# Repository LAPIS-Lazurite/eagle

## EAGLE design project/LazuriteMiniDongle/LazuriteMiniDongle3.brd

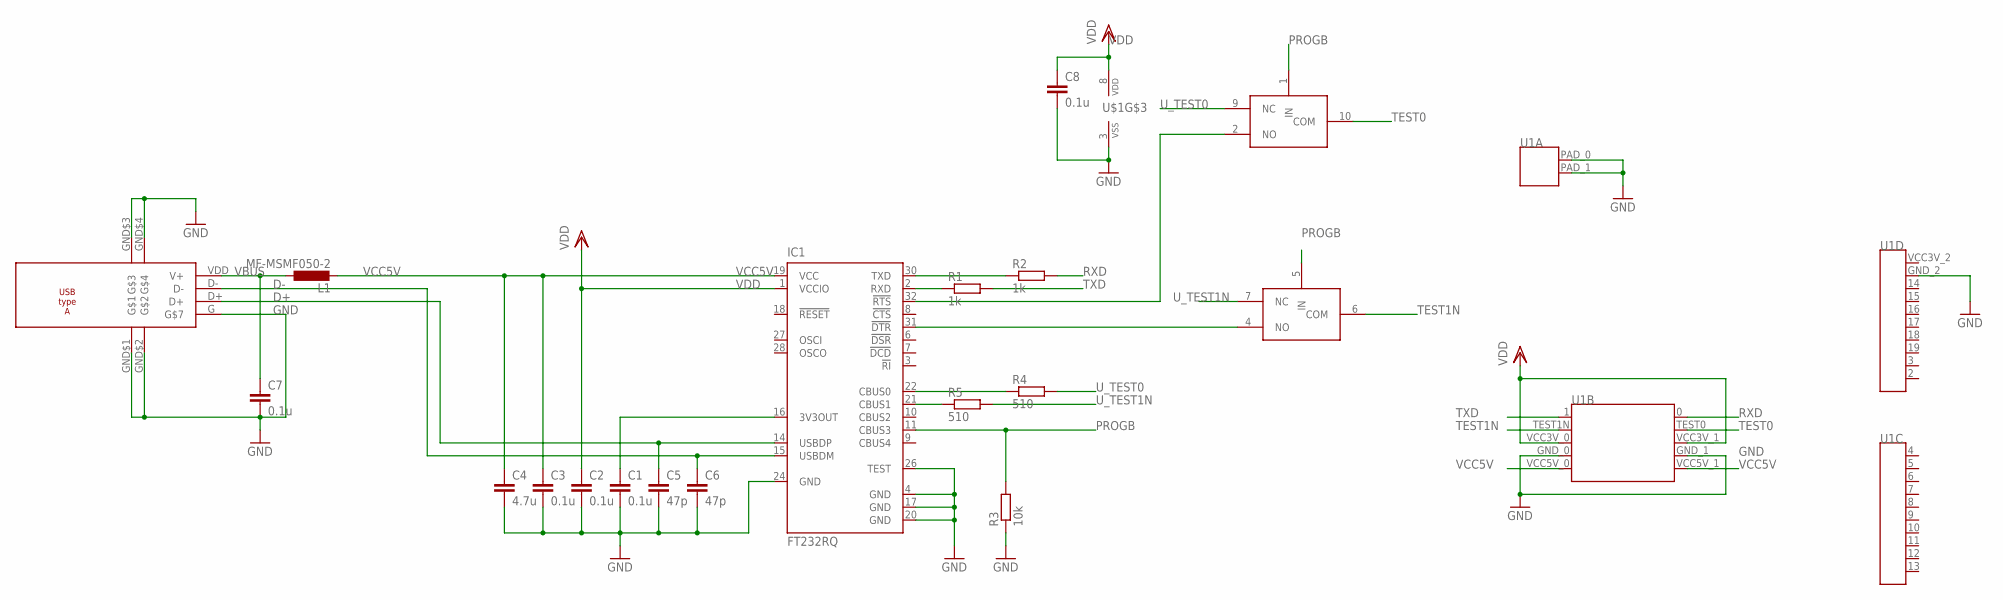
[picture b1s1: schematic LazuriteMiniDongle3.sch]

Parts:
C1, C2, C3, C7, C8: 0.1u; C0402
C4: 4.7u; C1608
C5, C6: 47p; C0402
IC1: FT232RQ; QFN32
L1: MF-MSMF050-2; L1812
R1, R2: 1k; R0402
R3: 10k; R0402
R4, R5: 510; R0402
U1: LAZURITE920JNOSILK; LAZURITE920J(NOSILK)
U$1: TI-TS5A23159; UQFN10
U$2: USB-TYPE-A; UP2-AH-TH

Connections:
D+: C5.1, IC1.14 (USBDP), U$2.D+
D-: C6.1, IC1.15 (USBDM), U$2.D-
GND: C1.2, C2.2, C3.2, C4.2, C5.2, C6.2, C7.2, C8.2, IC1.4 (GND), IC1.17 (GND), IC1.20 (GND), IC1.24 (GND), IC1.26 (TEST), R3.1, U1.GND_0, U1.GND_1, U1.GND_2, U1.PAD_0, U1.PAD_1, U$1.3 (VSS), U$2.G, U$2.GND$1, U$2.GND$2, U$2.GND$3, U$2.GND$4
unnamed: C1.1, IC1.16 (3V3OUT)
unnamed: IC1.32 (!RTS), U$1.2 (NO)
unnamed: IC1.2 (RXD), R1.1
unnamed: IC1.30 (TXD), R2.1
unnamed: IC1.21 (CBUS1), R5.1
unnamed: IC1.22 (CBUS0), R4.1
unnamed: IC1.31 (!DTR), U$1.4 (NO)
PROGB: IC1.11 (CBUS3), R3.2, U$1.1 (IN), U$1.5 (IN)
RXD: R2.2, U1.0
TEST0: U1.TEST0, U$1.10 (COM)
TEST1N: U1.TEST1N, U$1.6 (COM)
TXD: R1.2, U1.1
U_TEST0: R4.2, U$1.9 (NC)
U_TEST1N: R5.2, U$1.7 (NC)
VBUS: C7.1, L1.1, U$2.VDD (V+)
VCC5V: C3.1, C4.1, IC1.19 (VCC), L1.2, U1.VCC5V_0, U1.VCC5V_1
VDD: C2.1, C8.1, IC1.1 (VCCIO), U1.VCC3V_0, U1.VCC3V_1, U$1.8 (VDD)

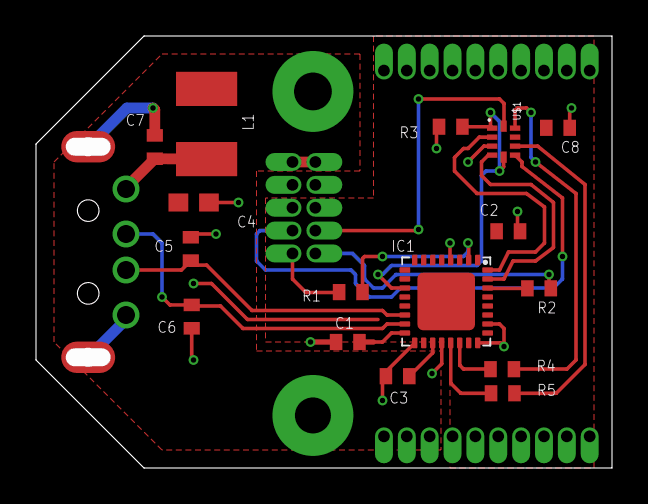
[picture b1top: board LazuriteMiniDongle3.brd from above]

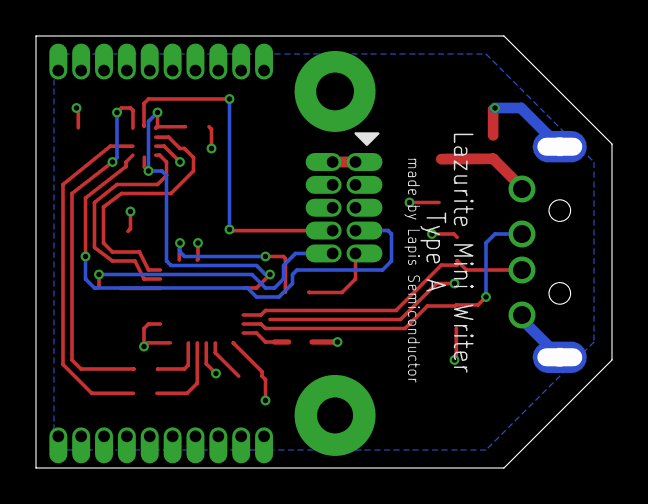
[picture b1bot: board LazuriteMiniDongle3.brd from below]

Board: 2 copper layers, 32.0 x 24.0 mm, 18 parts (2 on the bottom side), 20 nets.

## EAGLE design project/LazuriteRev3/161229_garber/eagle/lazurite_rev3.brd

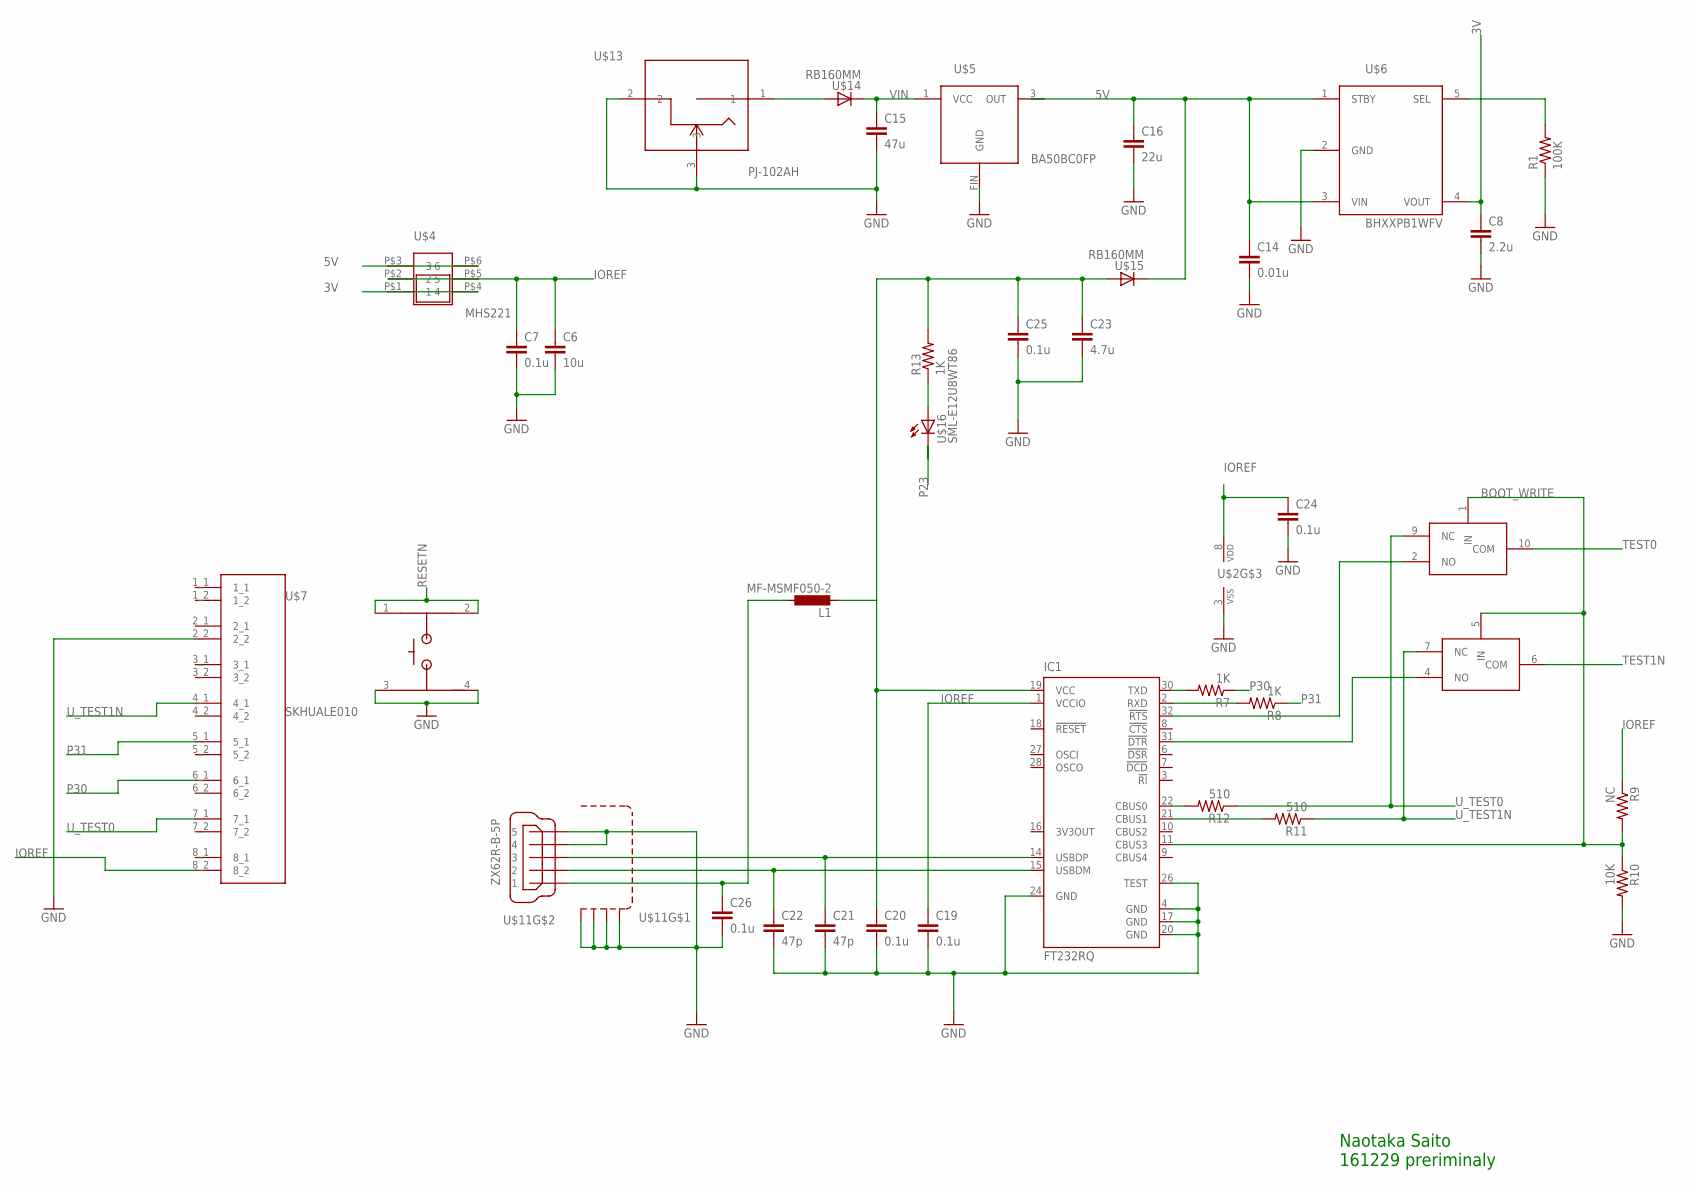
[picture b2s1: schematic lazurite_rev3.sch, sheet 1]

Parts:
C6: 10u; C0402
C7, C19, C20, C24, C25, C26: 0.1u; C0402
C8: 2.2u; C0402
C14: 0.01u; C0402
C15: 47u; C1210
C16: 22u; C1206
C21, C22: 47p; C0402
C23: 4.7u; C0402
IC1: FT232RQ; QFN32
L1: MF-MSMF050-2; L1812
R1: 100K; R0402
R7, R8, R13: 1K; R0402
R9: NC; R0402
R10: 10K; R0402
R11, R12: 510; R0402
U$2: TI-TS5A23159; UQFN10
U$4: MHS221
U$5: BA50BC0FP; TO252-3
U$6: BHXXPB1WFV; HVSOF5
U$7: SKHUALE010
U$11: ZX62R-B-5P
U$12: XB-1-X
U$13: PJ-102AH; PJ-102H
U$14, U$15: RB160MM; RB160MM-30
U$16: SML-E12U8WT86; SML-E1X

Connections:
3V: C8.1, U$4.P$1 (1), U$4.P$4 (4), U$6.4 (VOUT); also elsewhere on the board
5V: C14.1, C16.1, U$4.P$3 (3), U$4.P$6 (6), U$5.3 (OUT), U$6.1 (STBY), U$6.3 (VIN), U$15.C; also elsewhere on the board
BOOT_WRITE: IC1.11 (CBUS3), R9.2, R10.1, U$2.1 (IN), U$2.5 (IN)
DM: C22.1, IC1.15 (USBDM), U$11.2
DP: C21.1, IC1.14 (USBDP), U$11.3
GND: C6.2, C7.2, C8.2, C14.2, C15.2, C16.2, C19.2, C20.2, C21.2, C22.2, C23.2, C24.2, C25.2, C26.2, IC1.4 (GND), IC1.17 (GND), IC1.20 (GND), IC1.24 (GND), IC1.26 (TEST), R1.1, R10.2, U$2.3 (VSS), U$5.FIN (GND), U$6.2 (GND), U$7.3, U$7.4, U$11.4, U$11.5, U$11.M1 (S1), U$11.M2 (S2), U$11.M3 (S3), U$11.M4 (S4), U$12.2_2, U$13.2, U$13.3; also elsewhere on the board
IOREF: C6.1, C7.1, C19.1, C24.1, IC1.1 (VCCIO), R9.1, U$2.8 (VDD), U$4.P$2 (2), U$4.P$5 (5), U$12.8_2; also elsewhere on the board
unnamed: IC1.30 (TXD), R7.2
unnamed: IC1.22 (CBUS0), R12.2
unnamed: IC1.31 (!DTR), U$2.4 (NO)
unnamed: IC1.2 (RXD), R8.2
unnamed: IC1.21 (CBUS1), R11.2
unnamed: R1.2, U$6.5 (SEL)
unnamed: IC1.32 (!RTS), U$2.2 (NO)
unnamed: U$13.1, U$14.A
unnamed: R13.1, U$16.A
P23: U$16.C; also elsewhere on the board
P30: R7.1, U$12.6_1; also elsewhere on the board
P31: R8.1, U$12.5_1; also elsewhere on the board
RESETN: U$7.1, U$7.2; also elsewhere on the board
TEST0: U$2.10 (COM); also elsewhere on the board
TEST1N: U$2.6 (COM); also elsewhere on the board
USB5V: C26.1, L1.1, U$11.1
USBVDD: C20.1, C23.1, C25.1, IC1.19 (VCC), L1.2, R13.2, U$15.A
U_TEST0: R12.1, U$2.9 (NC), U$12.7_1
U_TEST1N: R11.1, U$2.7 (NC), U$12.4_1
VIN: C15.1, U$5.1 (VCC), U$14.C; also elsewhere on the board

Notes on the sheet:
Naotaka Saito 161229 preriminaly

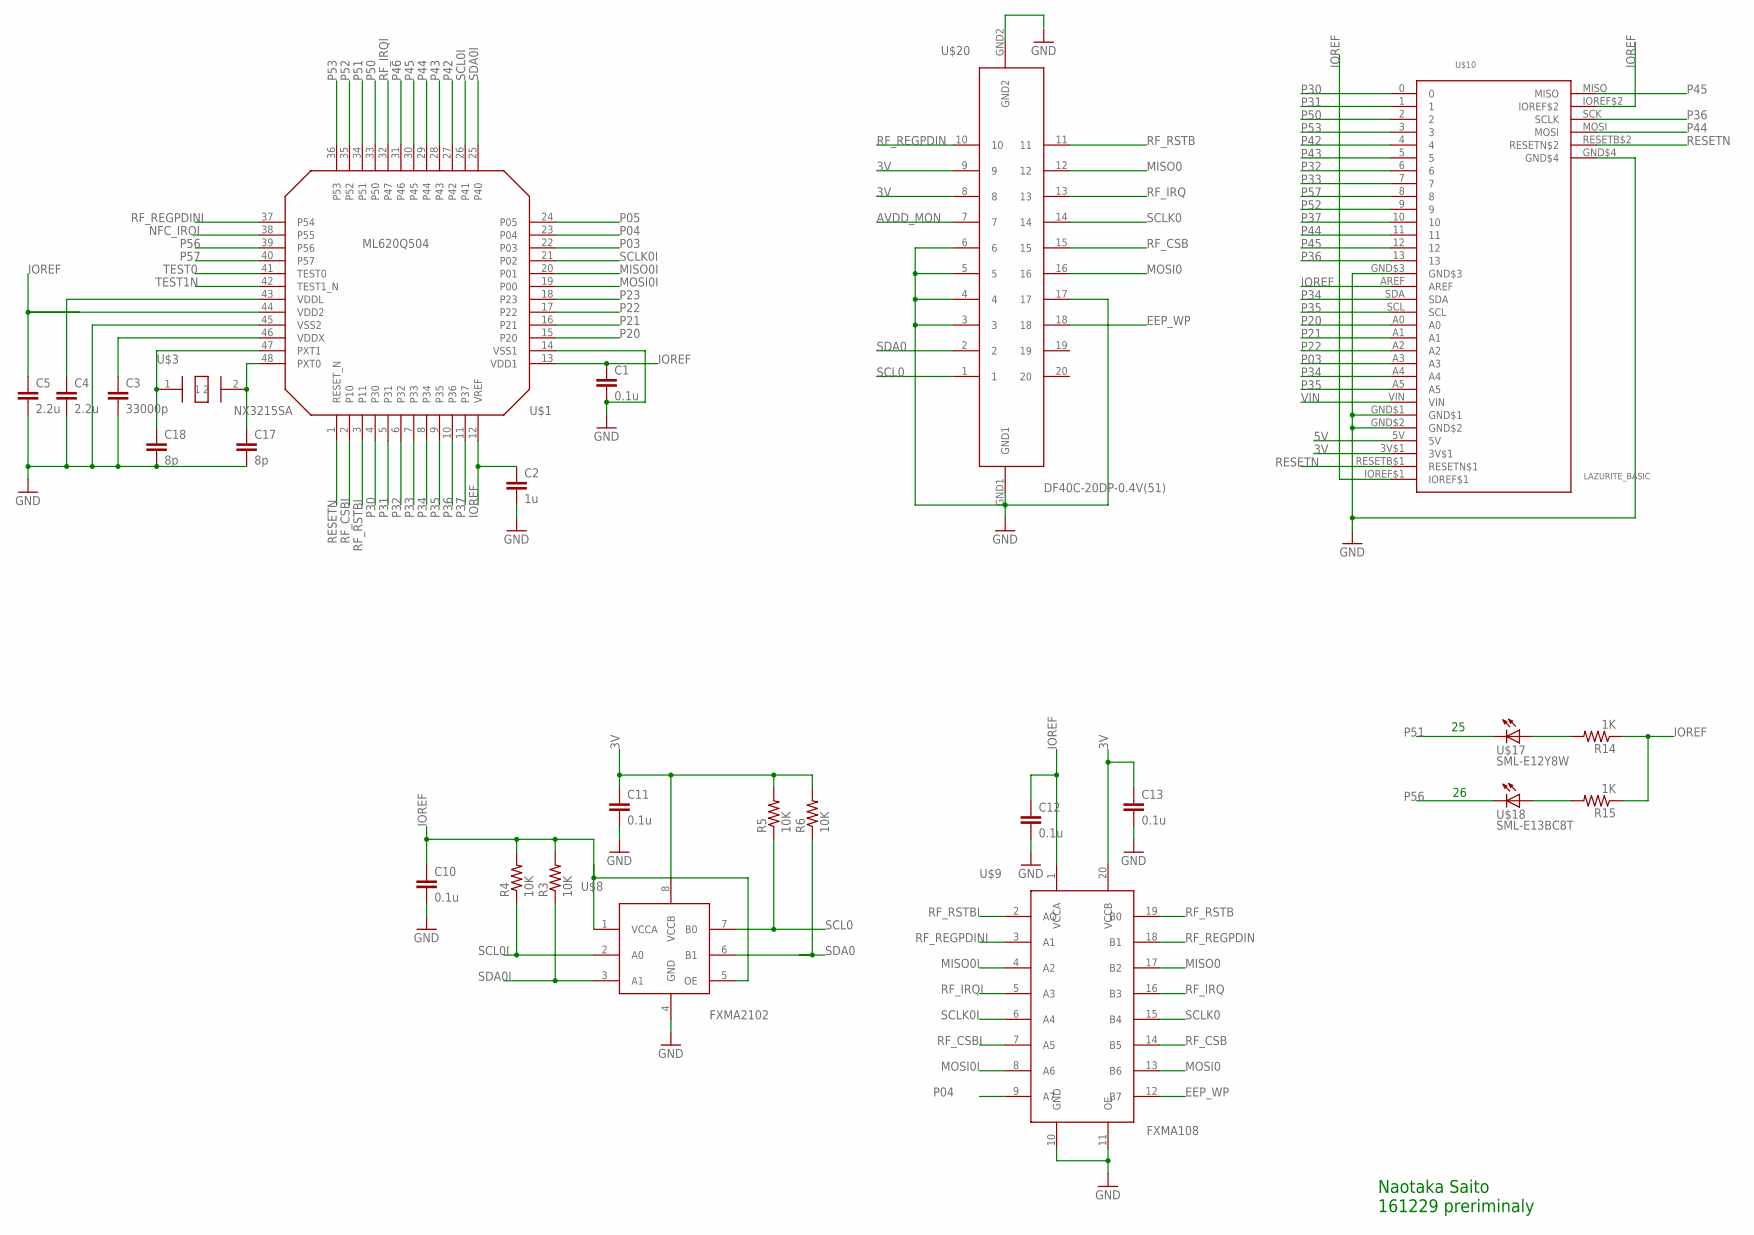
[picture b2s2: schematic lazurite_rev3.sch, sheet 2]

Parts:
C1, C10, C11, C12, C13: 0.1u; C0402
C2: 1u; C0402
C3: 33000p; C0402
C4, C5: 2.2u; C0402
C17, C18: 8p; C0402
R3, R4, R5, R6: 10K; R0402
R14, R15: 1K; R0402
U$1: ML620Q504
U$3: NX3215SA; NX3215SA-32,768K-SFD-MUA-14
U$8: FXMA2102; MICROPACK
U$9: FXMA108
U$10: LAZURITE_BASIC
U$17: SML-E12Y8W; SML-E1X
U$18: SML-E13BC8T; SML-E1X
U$20: DF40C-20DP-0.4V(51); BP3596A

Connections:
3V: C11.1, C13.1, R5.2, R6.2, U$8.8 (VCCB), U$9.20 (VCCB), U$10.3V$1, U$20.8, U$20.9; also elsewhere on the board
5V: U$10.5V; also elsewhere on the board
AVDD_MON: U$20.7
EEP_WP: U$9.12 (B7), U$20.18
GND: C1.2, C2.2, C3.2, C4.2, C5.2, C10.2, C11.2, C12.2, C13.2, C17.2, C18.2, U$1.14 (VSS1), U$1.45 (VSS2), U$8.4 (GND), U$9.10 (GND), U$9.11 (OE), U$10.GND$1, U$10.GND$2, U$10.GND$3, U$10.GND$4, U$20.3, U$20.4, U$20.5, U$20.6, U$20.17, U$20.GND1; also elsewhere on the board
IOREF: C1.1, C2.1, C5.1, C10.1, C12.1, R3.2, R4.2, R14.1, R15.1, U$1.12 (VREF), U$1.13 (VDD1), U$1.44 (VDD2), U$8.1 (VCCA), U$8.5 (OE), U$9.1 (VCCA), U$10.AREF, U$10.IOREF$1, U$10.IOREF$2; also elsewhere on the board
MISO0: U$9.17 (B2), U$20.12
MISO0I: U$1.20 (P01), U$9.4 (A2)
MOSI0: U$9.13 (B6), U$20.16
MOSI0I: U$1.19 (P00), U$9.8 (A6)
unnamed: C17.1, U$1.48 (PXT0), U$3.2
unnamed: C18.1, U$1.47 (PXT1), U$3.1
unnamed: C3.1, U$1.46 (VDDX)
unnamed: R14.2, U$17.A
unnamed: C4.1, U$1.43 (VDDL)
unnamed: R15.2, U$18.A
NFC_IRQI: U$1.38 (P55)
P03: U$1.22 (P03), U$10.A3
P04: U$1.23 (P04), U$9.9 (A7)
P05: U$1.24 (P05)
P20: U$1.15 (P20), U$10.A0
P21: U$1.16 (P21), U$10.A1
P22: U$1.17 (P22), U$10.A2
P23: U$1.18 (P23); also elsewhere on the board
P30: U$1.4 (P30), U$10.0; also elsewhere on the board
P31: U$1.5 (P31), U$10.1; also elsewhere on the board
P32: U$1.6 (P32), U$10.6
P33: U$1.7 (P33), U$10.7
P34: U$1.8 (P34), U$10.A4, U$10.SDA
P35: U$1.9 (P35), U$10.A5, U$10.SCL
P36: U$1.10 (P36), U$10.13, U$10.SCK (SCLK)
P37: U$1.11 (P37), U$10.10
P42: U$1.27 (P42), U$10.4
P43: U$1.28 (P43), U$10.5
P44: U$1.29 (P44), U$10.11, U$10.MOSI
P45: U$1.30 (P45), U$10.12, U$10.MISO
P46: U$1.31 (P46)
P50: U$1.33 (P50), U$10.2
P51: U$1.34 (P51), U$17.C
P52: U$1.35 (P52), U$10.9
P53: U$1.36 (P53), U$10.3
P56: U$1.39 (P56), U$18.C
P57: U$1.40 (P57), U$10.8
RESETN: U$1.1 (RESET_N), U$10.RESETB$1 (RESETN$1), U$10.RESETB$2 (RESETN$2); also elsewhere on the board
RF_CSB: U$9.14 (B5), U$20.15
RF_CSBI: U$1.2 (P10), U$9.7 (A5)
RF_IRQ: U$9.16 (B3), U$20.13
RF_IRQI: U$1.32 (P47), U$9.5 (A3)
RF_REGPDIN: U$9.18 (B1), U$20.10
RF_REGPDINI: U$1.37 (P54), U$9.3 (A1)
RF_RSTB: U$9.19 (B0), U$20.11
RF_RSTBI: U$1.3 (P11), U$9.2 (AO)
SCL0: R5.1, U$8.7 (B0), U$20.1
SCL0I: R4.1, U$1.26 (P41), U$8.2 (A0)
SCLK0: U$9.15 (B4), U$20.14
SCLK0I: U$1.21 (P02), U$9.6 (A4)
SDA0: R6.1, U$8.6 (B1), U$20.2
SDA0I: R3.1, U$1.25 (P40), U$8.3 (A1)
TEST0: U$1.41 (TEST0); also elsewhere on the board
TEST1N: U$1.42 (TEST1_N); also elsewhere on the board
VIN: U$10.VIN; also elsewhere on the board

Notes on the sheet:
Naotaka Saito 161229 preriminaly

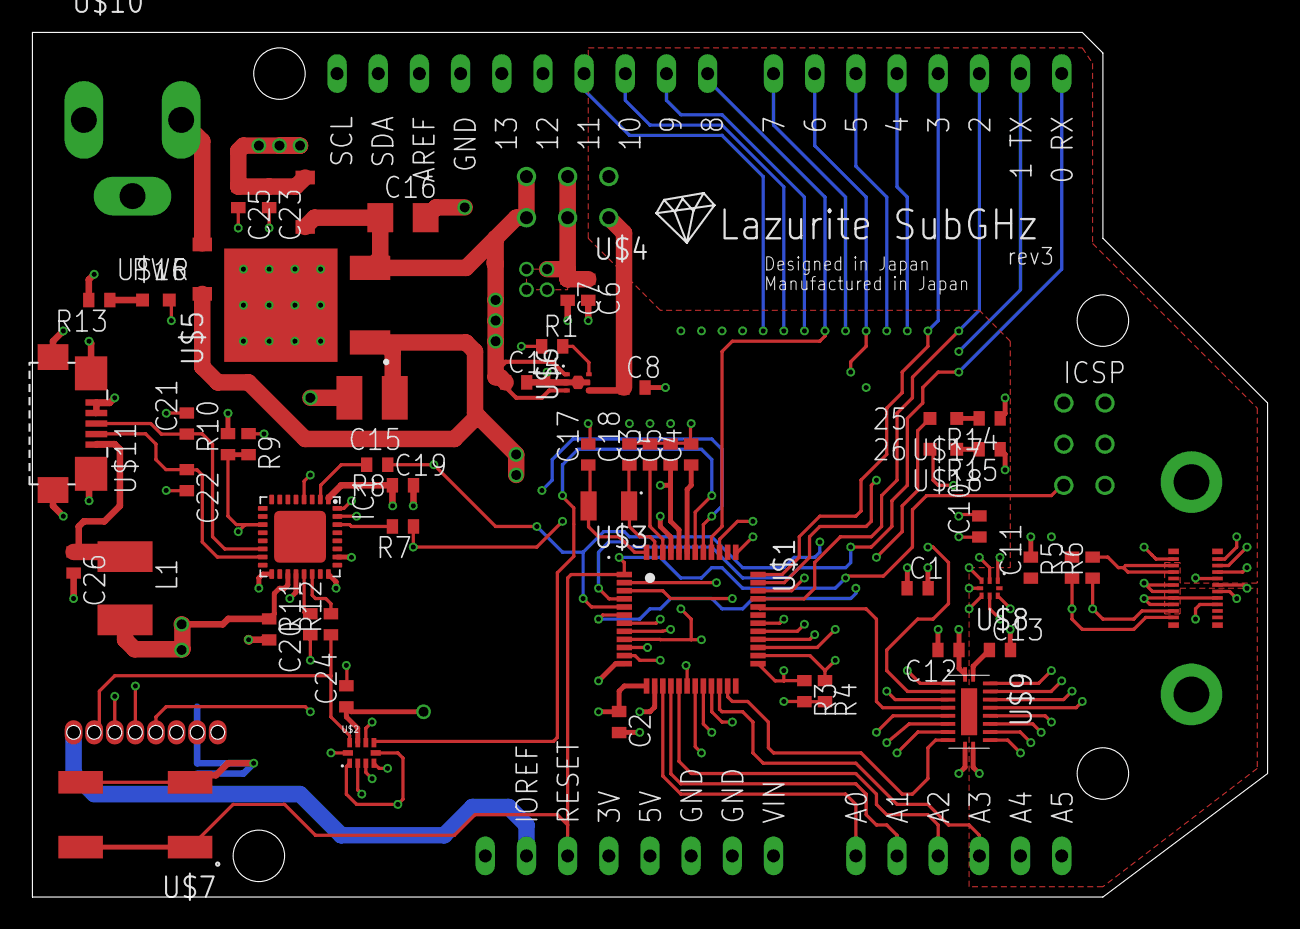
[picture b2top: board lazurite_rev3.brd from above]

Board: 4 copper layers, 76.2 x 53.3 mm, 62 parts (1 on the bottom side), 73 nets.

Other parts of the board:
U$19: LOGO
U$21: QRCODE

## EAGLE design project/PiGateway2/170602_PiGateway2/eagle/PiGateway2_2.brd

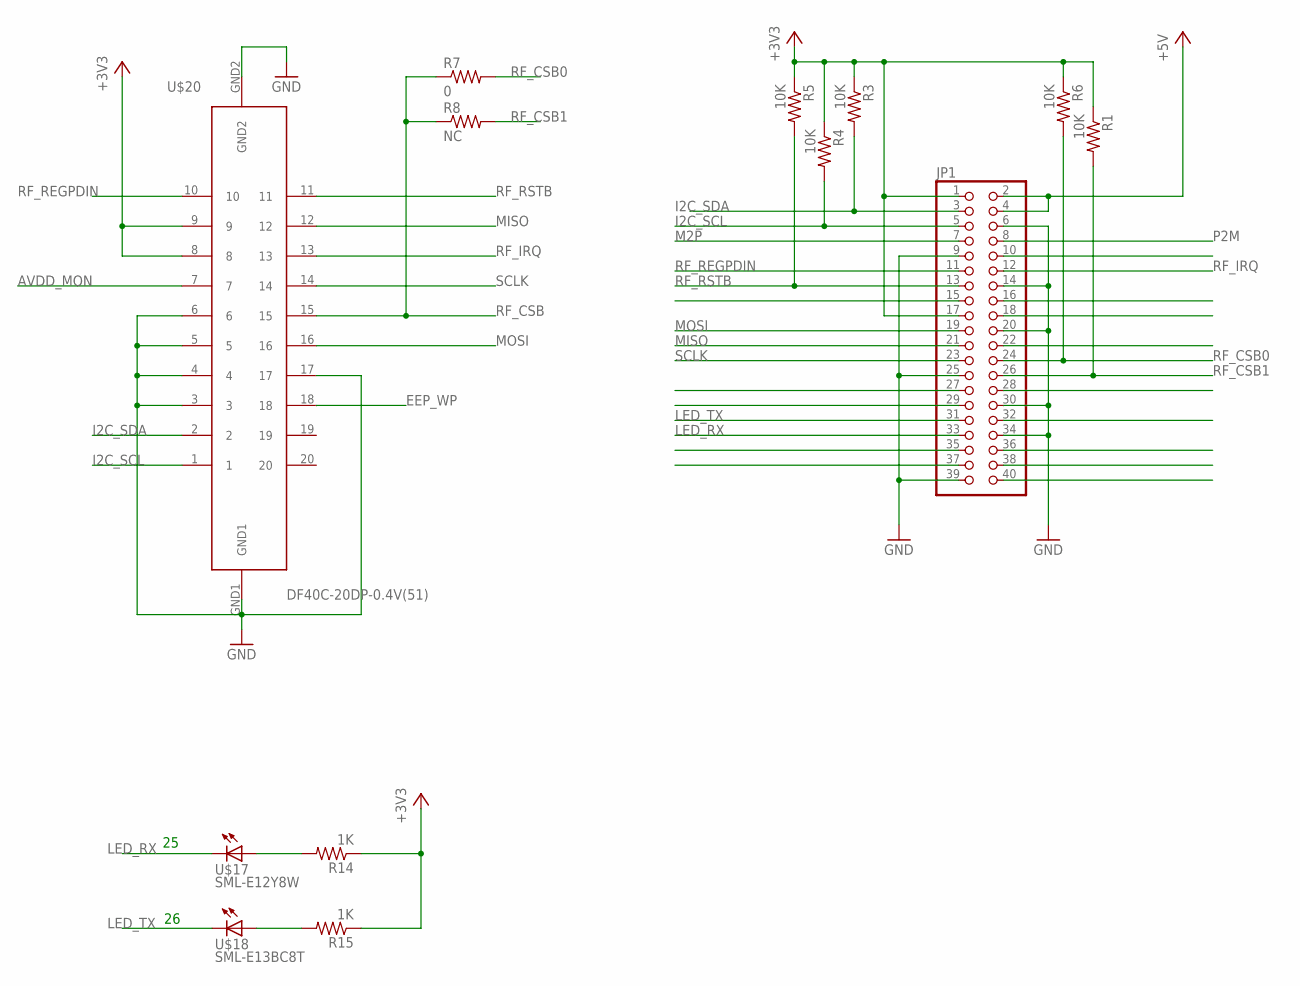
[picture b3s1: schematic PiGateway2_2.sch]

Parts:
JP1: PINHD-2X20; 2X20
R1, R3, R4, R5, R6: 10K; R0402
R7: 0; R0402
R8: NC; R0402
R14, R15: 1K; R0402
U$17: SML-E12Y8W; SML-E1X
U$18: SML-E13BC8T; SML-E1X
U$20: DF40C-20DP-0.4V(51); BP3596A

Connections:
+3V3: JP1.1, JP1.17, R1.1, R3.1, R4.1, R5.1, R6.1, R14.1, R15.1, U$20.8, U$20.9
+5V: JP1.2, JP1.4
AVDD_MON: U$20.7
EEP_WP: U$20.18
GND: JP1.6, JP1.9, JP1.14, JP1.20, JP1.25, JP1.30, JP1.34, JP1.39, U$20.3, U$20.4, U$20.5, U$20.6, U$20.17, U$20.GND1, U$20.GND2
I2C_SCL: JP1.5, R4.2, U$20.1
I2C_SDA: JP1.3, R3.2, U$20.2
LED_RX: JP1.33, U$17.C
LED_TX: JP1.31, U$18.C
M2P: JP1.7
MISO: JP1.21, U$20.12
MOSI: JP1.19, U$20.16
unnamed: R14.2, U$17.A
unnamed: R15.2, U$18.A
P2M: JP1.8
RF_CSB: R7.1, R8.1, U$20.15
RF_CSB0: JP1.24, R6.2, R7.2
RF_CSB1: JP1.26, R1.2, R8.2
RF_IRQ: JP1.12, U$20.13
RF_REGPDIN: JP1.11, U$20.10
RF_RSTB: JP1.13, R5.2, U$20.11
SCLK: JP1.23, U$20.14

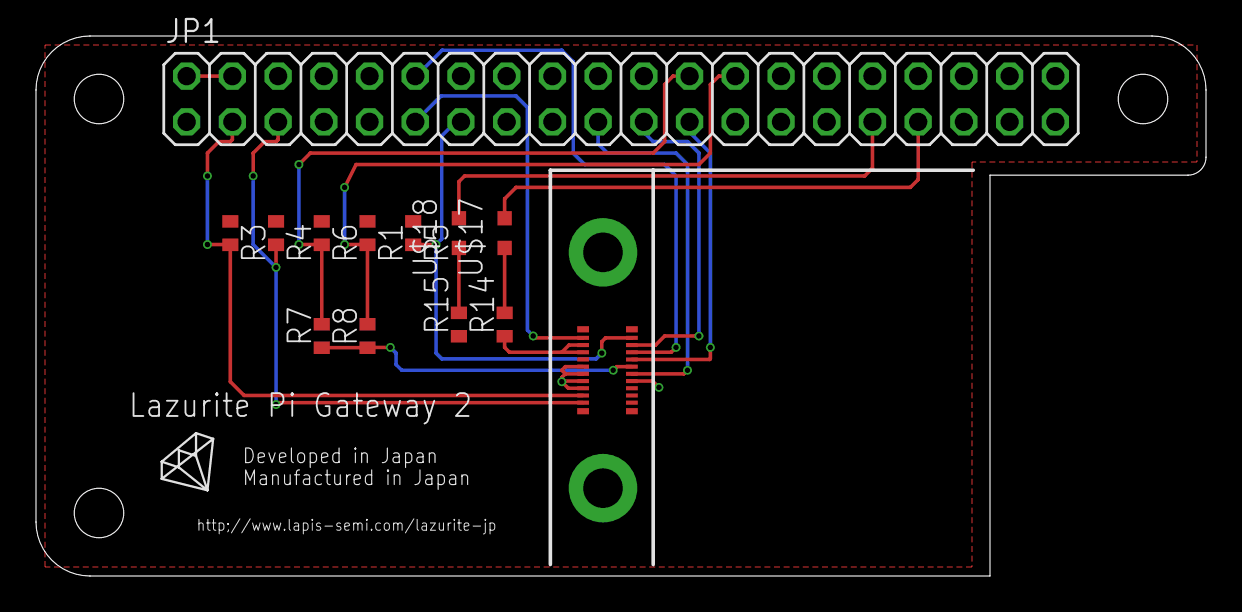
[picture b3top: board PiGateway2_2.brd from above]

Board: 2 copper layers, 65.0 x 30.0 mm, 14 parts (0 on the bottom side), 18 nets.

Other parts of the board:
U$1: LOGO
